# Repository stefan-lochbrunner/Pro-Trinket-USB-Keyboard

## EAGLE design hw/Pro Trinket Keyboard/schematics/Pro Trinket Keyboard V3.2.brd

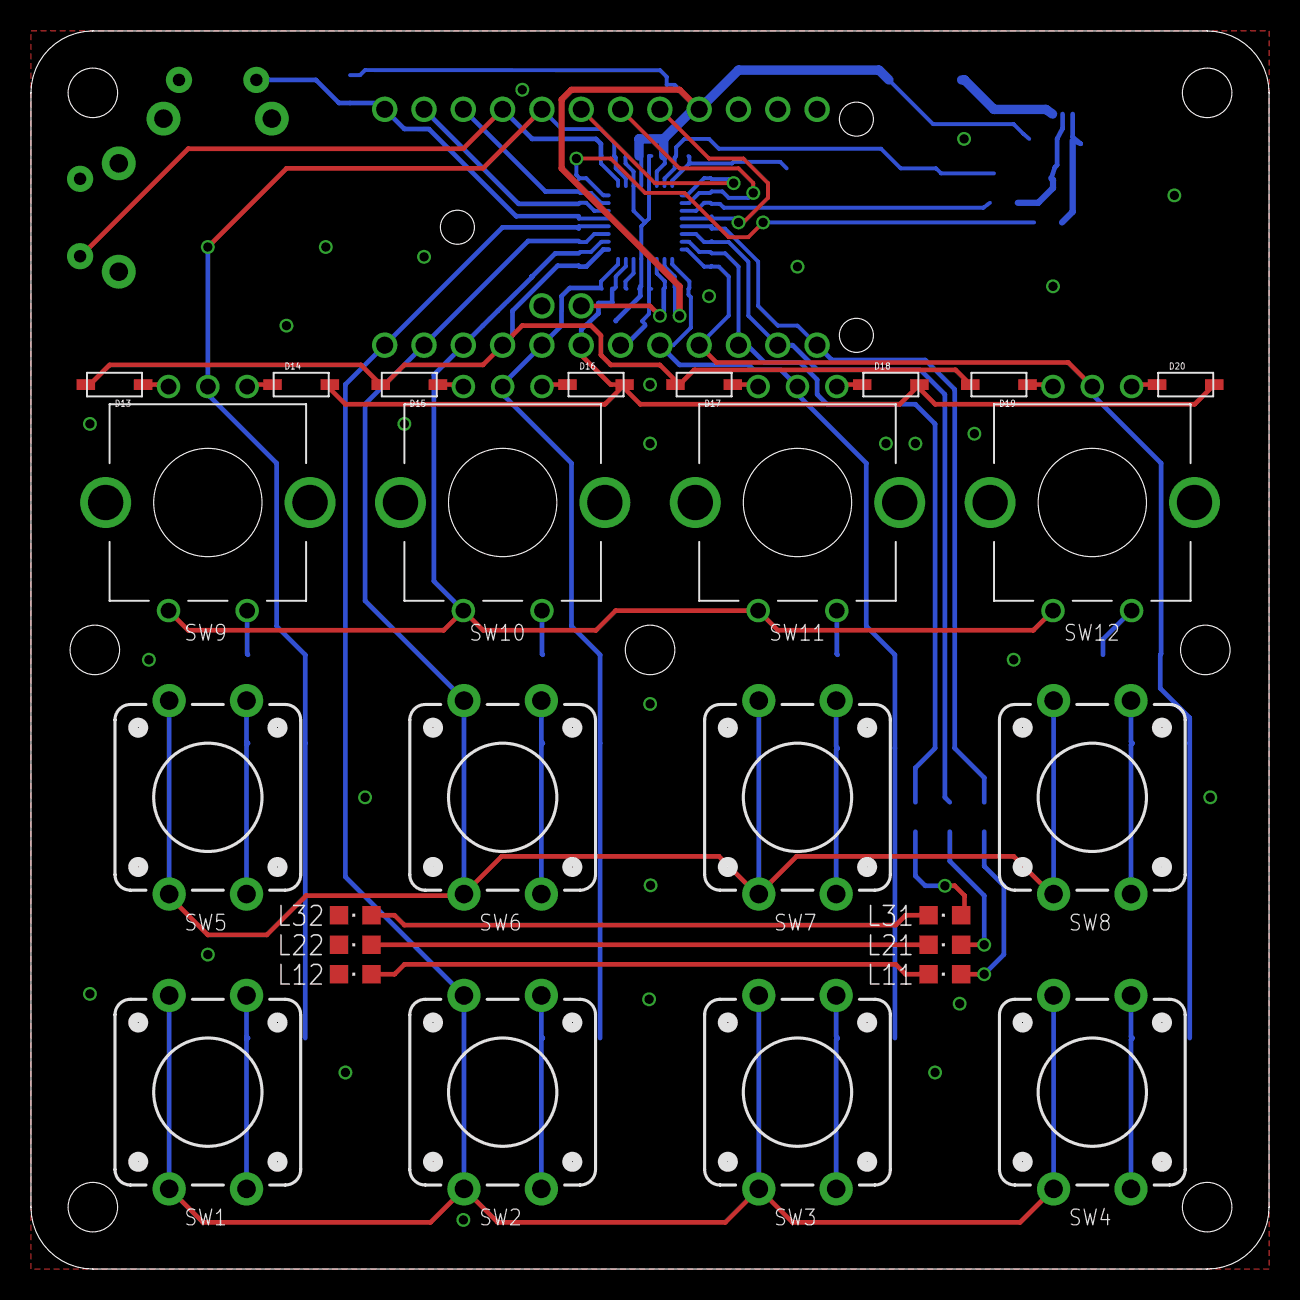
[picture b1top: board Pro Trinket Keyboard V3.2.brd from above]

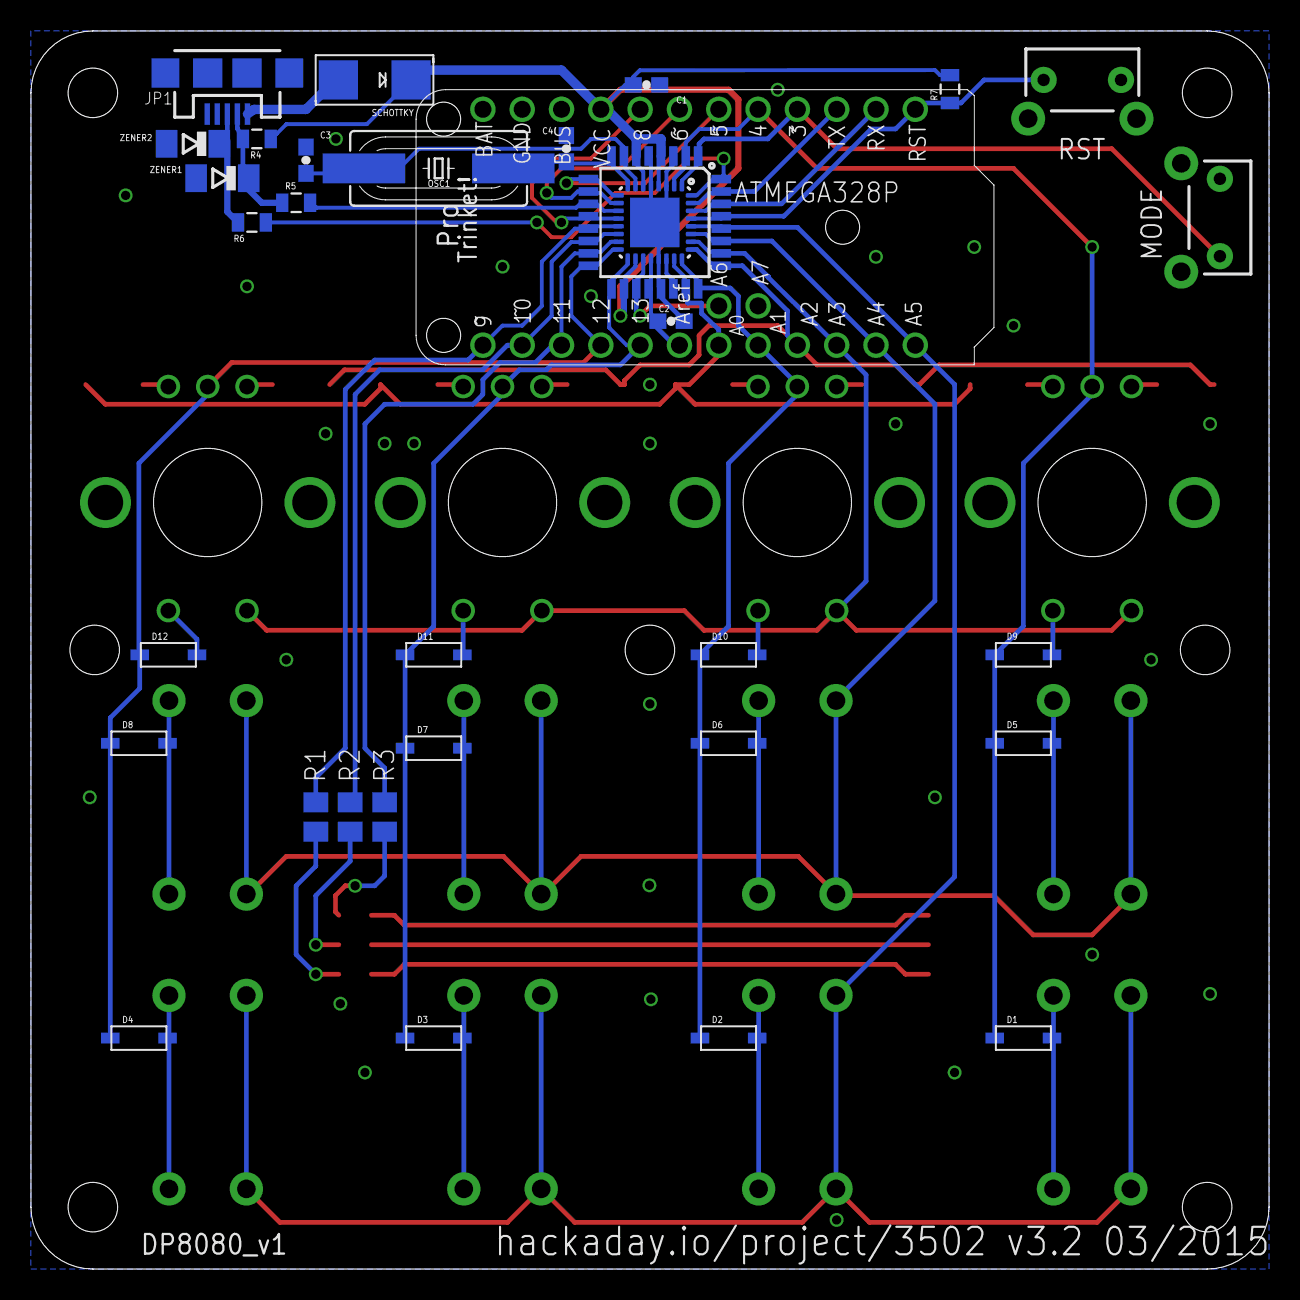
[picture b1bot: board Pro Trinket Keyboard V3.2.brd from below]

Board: 2 copper layers, 80.0 x 80.0 mm, 60 parts (33 on the bottom side), 57 nets.

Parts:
ATMEGA328P: MLF32-PAD
ATMEGA328P_TQFP: TQFP32-08
C1: 10uF; 0603-CAP
C2: 0.1uF; 0603-CAP
C3, C4: 22pF; 0603-CAP
D1, D2, D3, D4, D5, D6, D7, D8, D9, D10, D11, D12, D13, D14, D15, D16, D17, D18, D19, D20: SOD-123
JP1: USB-MICROB
L11, L12, L21, L22, L31, L32: CHIPLED_0805
MODE: TACTILE-PTH-SIDEEZ
OSC1: 16MHz; HC-49U
R1: 62; M0805
R2: 39; M0805
R3: 20; M0805
R4: 1.5k; 0805
R5, R6: 68; 0805
R7: 10k; 0805
RST: TACTILE-PTH-SIDEEZ
S1, S2, S3, S4, S5, S6, S7, S8: TACTILE-PTH-12MM
SCHOTTKY: SMADIODE
SW9, SW10, SW11, SW12: ROTARTY_ENCODER; ROTARY_ENC_PLAIN
U$1: DP8080_V1
U$2: PRO_TRINKET; PROTRINKET
ZENER1, ZENER2: 3.6V; SOD80C

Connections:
A0/D14: ATMEGA328P.23, ATMEGA328P_TQFP.23, D14.A, D16.A, D18.A, D20.A, U$2.A0
A1/D15: ATMEGA328P.24, ATMEGA328P_TQFP.24, D2.C, D6.C, D10.C, SW10.C, U$2.A1
A2/D16: ATMEGA328P.25, ATMEGA328P_TQFP.25, D13.A, D15.A, D17.A, D19.A, U$2.A2
A3/D17: ATMEGA328P.26, ATMEGA328P_TQFP.26, SW9.SW+, SW10.SW+, SW11.SW+, SW12.SW+, U$2.A3
A4/D18: ATMEGA328P.27, ATMEGA328P_TQFP.27, S5.1, S5.2, S6.1, S6.2, S7.1, S7.2, S8.1, S8.2, U$2.A4
A5/D19: ATMEGA328P.28, ATMEGA328P_TQFP.28, S1.1, S1.2, S2.1, S2.2, S3.1, S3.2, S4.1, S4.2, U$2.A5
A6: ATMEGA328P.19, ATMEGA328P_TQFP.19, U$2.A6
A7: ATMEGA328P.22, ATMEGA328P_TQFP.22
AREF: ATMEGA328P.20, ATMEGA328P_TQFP.20, C2.2, U$2.AREF
D2/D+: ATMEGA328P.32, ATMEGA328P_TQFP.32, R6.2
D3: ATMEGA328P.1, ATMEGA328P_TQFP.1, MODE.1, U$2.3
D4: ATMEGA328P.2, ATMEGA328P_TQFP.2, D1.C, D5.C, D9.C, SW9.C, U$2.4
D5: ATMEGA328P.9, ATMEGA328P_TQFP.9, U$2.5
D6: ATMEGA328P.10, ATMEGA328P_TQFP.10, U$2.6
D7/D-: ATMEGA328P.11, ATMEGA328P_TQFP.11, R5.2
D8: ATMEGA328P.12, ATMEGA328P_TQFP.12, U$2.8
D9: ATMEGA328P.13, ATMEGA328P_TQFP.13, R1.2, U$2.9
D10: ATMEGA328P.14, ATMEGA328P_TQFP.14, R2.2, U$2.10
D11: ATMEGA328P.15, ATMEGA328P_TQFP.15, R3.2, U$2.11
D12: ATMEGA328P.16, ATMEGA328P_TQFP.16, D4.C, D8.C, D12.C, SW12.C, U$2.12
D13: ATMEGA328P.17, ATMEGA328P_TQFP.17, D3.C, D7.C, D11.C, SW11.C, U$2.13
GND: ATMEGA328P.3, ATMEGA328P.5, ATMEGA328P.21, ATMEGA328P.PAD, ATMEGA328P_TQFP.3, ATMEGA328P_TQFP.5, ATMEGA328P_TQFP.21, C1.1, C2.1, C3.1, C4.2, JP1.GND, JP1.MT1, JP1.MT2, L12.C, L22.C, L32.C, MODE.2, RST.1, U$2.GND, ZENER1.A, ZENER2.A
L31: L31.C, L32.A
unnamed: L11.A, R1.1
unnamed: L11.C, L12.A
unnamed: L21.A, R2.1
unnamed: L21.C, L22.A
unnamed: L31.A, R3.1
unnamed: JP1.VBUS, SCHOTTKY.A
unnamed: JP1.D-, R4.1, R5.1, ZENER1.C
unnamed: JP1.D+, R6.1, ZENER2.C
unnamed: D1.A, S1.3, S1.4
unnamed: D2.A, S2.3, S2.4
unnamed: D5.A, S5.3, S5.4
unnamed: D6.A, S6.3, S6.4
unnamed: D7.A, S7.3, S7.4
unnamed: D3.A, S3.3, S3.4
unnamed: D4.A, S4.3, S4.4
unnamed: D8.A, S8.3, S8.4
unnamed: D10.A, SW10.SW-
unnamed: D9.A, SW9.SW-
unnamed: D11.A, SW11.SW-
unnamed: D20.C, SW12.A
unnamed: D19.C, SW12.B
unnamed: D18.C, SW11.A
unnamed: D12.A, SW12.SW-
unnamed: D16.C, SW10.A
unnamed: D15.C, SW10.B
unnamed: D14.C, SW9.A
unnamed: D13.C, SW9.B
unnamed: D17.C, SW11.B
RST: ATMEGA328P.29, ATMEGA328P_TQFP.29, R7.1, RST.2, U$2.RST
RX: ATMEGA328P.30, ATMEGA328P_TQFP.30, U$2.RX
TX: ATMEGA328P.31, ATMEGA328P_TQFP.31, U$2.TX
VCC: ATMEGA328P.4, ATMEGA328P.6, ATMEGA328P.18, ATMEGA328P_TQFP.4, ATMEGA328P_TQFP.6, ATMEGA328P_TQFP.18, C1.2, R4.2, R7.2, SCHOTTKY.C, U$2.VCC
XTAL1: ATMEGA328P.7, ATMEGA328P_TQFP.7, C3.2, OSC1.2
XTAL2: ATMEGA328P.8, ATMEGA328P_TQFP.8, C4.1, OSC1.1

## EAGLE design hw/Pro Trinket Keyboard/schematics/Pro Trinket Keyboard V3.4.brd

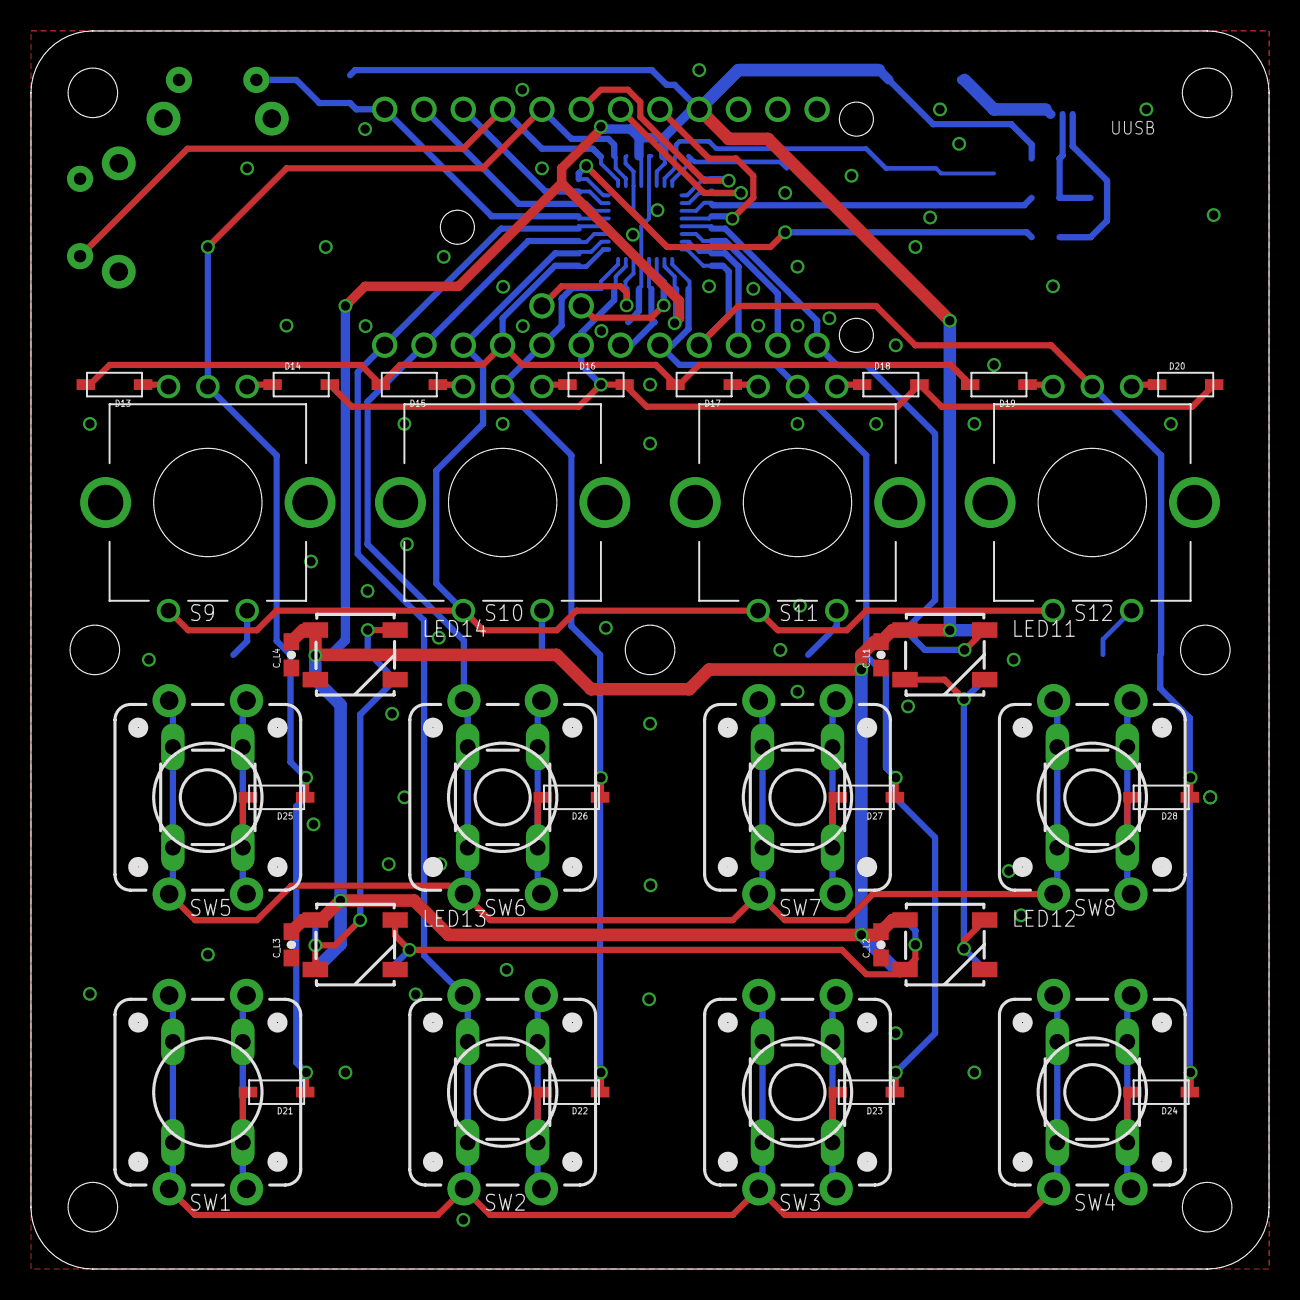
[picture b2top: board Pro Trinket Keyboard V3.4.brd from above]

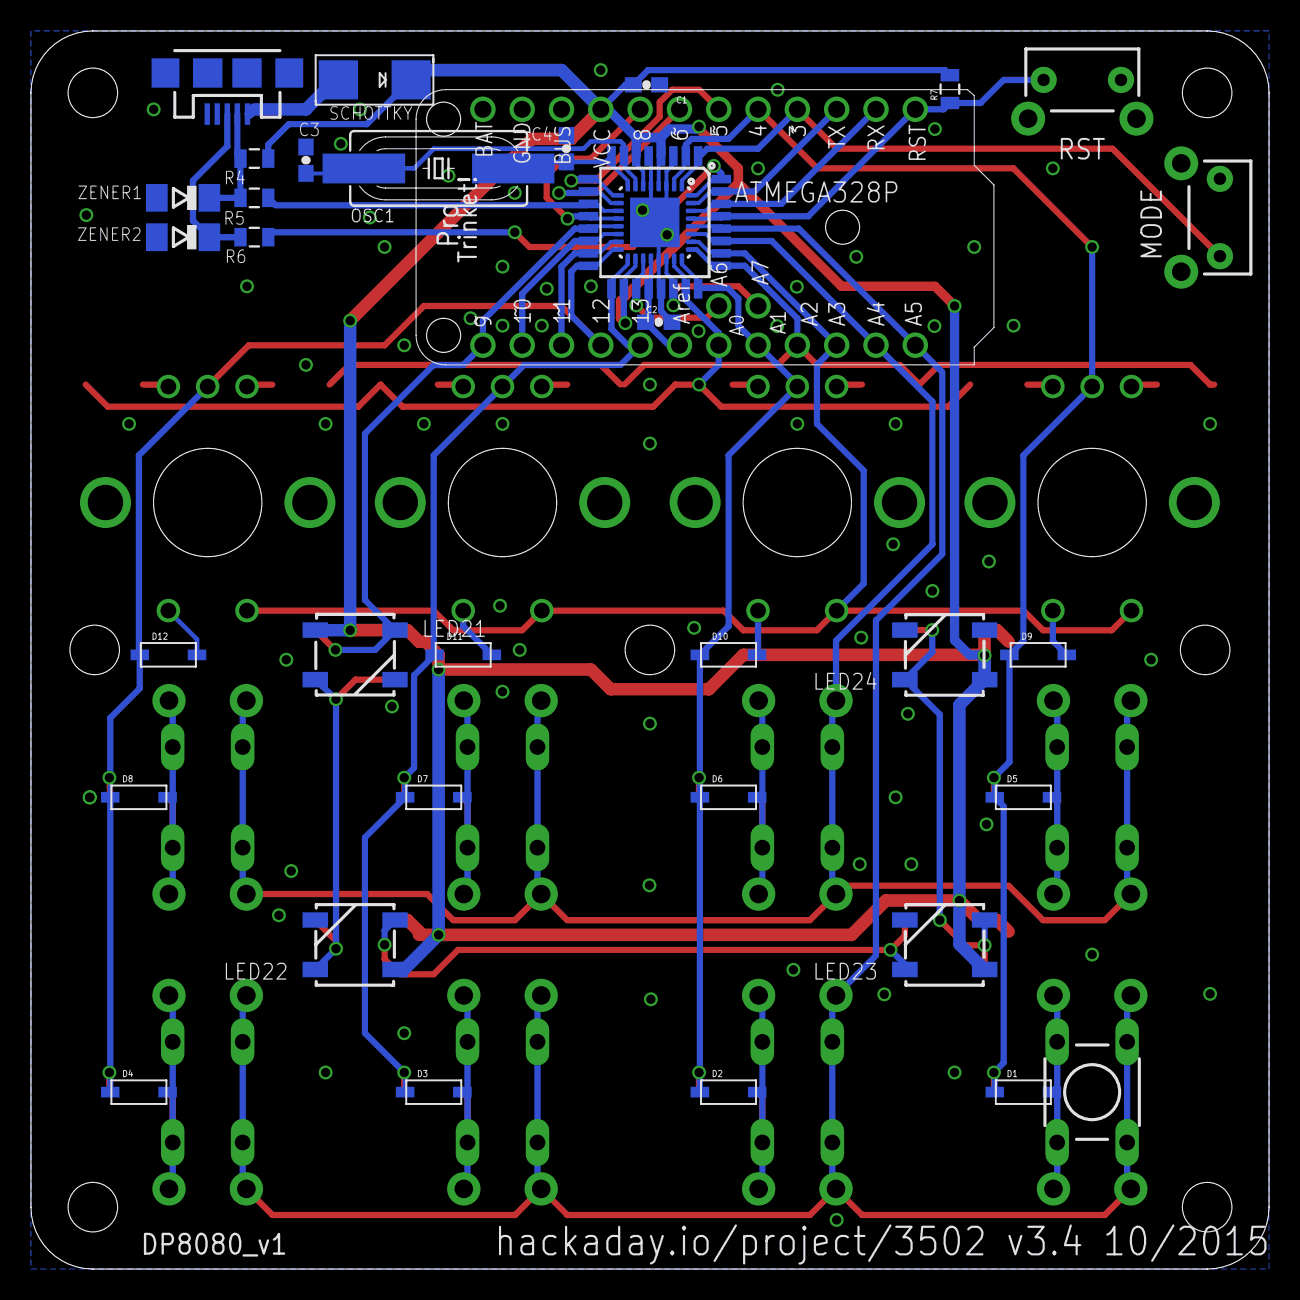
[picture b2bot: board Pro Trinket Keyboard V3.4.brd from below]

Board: 2 copper layers, 80.0 x 80.0 mm, 79 parts (35 on the bottom side), 54 nets.

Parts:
ATMEGA328P: MLF32-PAD
ATMEGA328P_TQFP: TQFP32-08
C1: 10uF; 0603-CAP
C2: 0.1uF; 0603-CAP
C3, C4: 22pF; 0603-CAP
C_L1, C_L2, C_L3, C_L4: 0.1uF; 0603-CAP
D1, D2, D3, D4, D5, D6, D7, D8, D9, D10, D11, D12, D13, D14, D15, D16, D17, D18, D19, D20, D21, D22, D23, D24, D25, D26, D27, D28: SOD-123
LED11, LED12, LED13, LED14, LED21, LED22, LED23, LED24: WS2812B
MODE: TACTILE-PTH-SIDEEZ
OSC1: 16MHz; HC-49U
R4: 1.5k; 0805
R5, R6: 68; 0805
R7: 10k; 0805
RST: TACTILE-PTH-SIDEEZ
S1, S2, S3, S4, S5, S6, S7, S8: TACTILE-PTH-12MM
S9, S10, S11, S12: ROTARTY_ENCODER; ROTARY_ENC_PLAIN
SCHOTTKY: SMADIODE
SW1, SW2, SW3, SW4, SW5, SW6, SW7, SW8: TAC-SWITCH-PTH
U$1: DP8080_V1
U$2: PRO_TRINKET; PROTRINKET
UUSB: USB-MICROB
ZENER1, ZENER2: 3.6V; SOD80C

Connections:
A0/D14: ATMEGA328P.23, ATMEGA328P_TQFP.23, D14.A, D16.A, D18.A, D20.A, U$2.A0
A1/D15: ATMEGA328P.24, ATMEGA328P_TQFP.24, D2.C, D6.C, D10.C, D22.C, D26.C, S10.C, U$2.A1
A2/D16: ATMEGA328P.25, ATMEGA328P_TQFP.25, D13.A, D15.A, D17.A, D19.A, U$2.A2
A3/D17: ATMEGA328P.26, ATMEGA328P_TQFP.26, S9.SW+, S10.SW+, S11.SW+, S12.SW+, U$2.A3
A4/D18: ATMEGA328P.27, ATMEGA328P_TQFP.27, S5.1, S5.2, S6.1, S6.2, S7.1, S7.2, S8.1, S8.2, SW5.1, SW5.2, SW6.1, SW6.2, SW7.1, SW7.2, SW8.1, SW8.2, U$2.A4
A5/D19: ATMEGA328P.28, ATMEGA328P_TQFP.28, S1.1, S1.2, S2.1, S2.2, S3.1, S3.2, S4.1, S4.2, SW1.1, SW1.2, SW2.1, SW2.2, SW3.1, SW3.2, SW4.1, SW4.2, U$2.A5
A6: ATMEGA328P.19, ATMEGA328P_TQFP.19, U$2.A6
A7: ATMEGA328P.22, ATMEGA328P_TQFP.22, U$2.A7
AREF: ATMEGA328P.20, ATMEGA328P_TQFP.20, C2.2, U$2.AREF
D2/D+: ATMEGA328P.32, ATMEGA328P_TQFP.32, R6.2
D3: ATMEGA328P.1, ATMEGA328P_TQFP.1, MODE.1, U$2.3
D4: ATMEGA328P.2, ATMEGA328P_TQFP.2, D1.C, D5.C, D9.C, D21.C, D25.C, S9.C, U$2.4
D5: ATMEGA328P.9, ATMEGA328P_TQFP.9, U$2.5
D6: ATMEGA328P.10, ATMEGA328P_TQFP.10, U$2.6
D7/D-: ATMEGA328P.11, ATMEGA328P_TQFP.11, R5.2
D8: ATMEGA328P.12, ATMEGA328P_TQFP.12, U$2.8
D9: ATMEGA328P.13, ATMEGA328P_TQFP.13, LED11.4, LED21.4, U$2.9
D10: ATMEGA328P.14, ATMEGA328P_TQFP.14, U$2.10
D11: ATMEGA328P.15, ATMEGA328P_TQFP.15, U$2.11
D12: ATMEGA328P.16, ATMEGA328P_TQFP.16, D4.C, D8.C, D12.C, D24.C, D28.C, S12.C, U$2.12
D13: ATMEGA328P.17, ATMEGA328P_TQFP.17, D3.C, D7.C, D11.C, D23.C, D27.C, S11.C, U$2.13
GND: ATMEGA328P.3, ATMEGA328P.5, ATMEGA328P.21, ATMEGA328P.PAD, ATMEGA328P_TQFP.3, ATMEGA328P_TQFP.5, ATMEGA328P_TQFP.21, C1.1, C2.1, C3.1, C4.2, C_L1.1, C_L2.1, C_L3.1, C_L4.1, LED11.3, LED12.3, LED13.3, LED14.3, LED21.3, LED22.3, LED23.3, LED24.3, MODE.2, RST.1, U$2.GND, UUSB.GND, UUSB.MT1, UUSB.MT2, ZENER1.A, ZENER2.A
L1NODE: LED11.2, LED12.4, LED21.2, LED22.4
L2NODE: LED12.2, LED13.4, LED22.2, LED23.4
L3NODE: LED13.2, LED14.4, LED23.2, LED24.4
unnamed: SCHOTTKY.A, UUSB.VBUS
unnamed: R4.1, R5.1, UUSB.D-, ZENER1.C
unnamed: R6.1, UUSB.D+, ZENER2.C
unnamed: D10.A, S10.SW-
unnamed: D9.A, S9.SW-
unnamed: D11.A, S11.SW-
unnamed: D20.C, S12.A
unnamed: D19.C, S12.B
unnamed: D18.C, S11.A
unnamed: D12.A, S12.SW-
unnamed: D16.C, S10.A
unnamed: D15.C, S10.B
unnamed: D14.C, S9.A
unnamed: D13.C, S9.B
unnamed: D17.C, S11.B
RST: ATMEGA328P.29, ATMEGA328P_TQFP.29, R7.1, RST.2, U$2.RST
RX: ATMEGA328P.30, ATMEGA328P_TQFP.30, U$2.RX
S1NODE: D1.A, D21.A, S1.3, S1.4, SW1.3, SW1.4
S2NODE: D2.A, D22.A, S2.3, S2.4, SW2.3, SW2.4
S3NODE: D3.A, D23.A, S3.3, S3.4, SW3.3, SW3.4
S4NODE: D4.A, D24.A, S4.3, S4.4, SW4.3, SW4.4
S5NODE: D5.A, D25.A, S5.3, S5.4, SW5.3, SW5.4
S6NODE: D6.A, D26.A, S6.3, S6.4, SW6.3, SW6.4
S7NODE: D7.A, D27.A, S7.3, S7.4, SW7.3, SW7.4
S8NODE: D8.A, D28.A, S8.3, S8.4, SW8.3, SW8.4
TX: ATMEGA328P.31, ATMEGA328P_TQFP.31, U$2.TX
VCC: ATMEGA328P.4, ATMEGA328P.6, ATMEGA328P.18, ATMEGA328P_TQFP.4, ATMEGA328P_TQFP.6, ATMEGA328P_TQFP.18, C1.2, C_L1.2, C_L2.2, C_L3.2, C_L4.2, LED11.1, LED12.1, LED13.1, LED14.1, LED21.1, LED22.1, LED23.1, LED24.1, R4.2, R7.2, SCHOTTKY.C, U$2.VCC
XTAL1: ATMEGA328P.7, ATMEGA328P_TQFP.7, C3.2, OSC1.2
XTAL2: ATMEGA328P.8, ATMEGA328P_TQFP.8, C4.1, OSC1.1

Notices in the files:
parts and their libraries:
SparkFun-Electromechanical: Licensing: CC v3.0 Share-Alike You are welcome to use this library for commercial purposes.
SparkFun-DigitalIC: Licensing: Creative Commons ShareAlike 4.0 International - https://creativecommons.org/licenses/by-sa/4.0
